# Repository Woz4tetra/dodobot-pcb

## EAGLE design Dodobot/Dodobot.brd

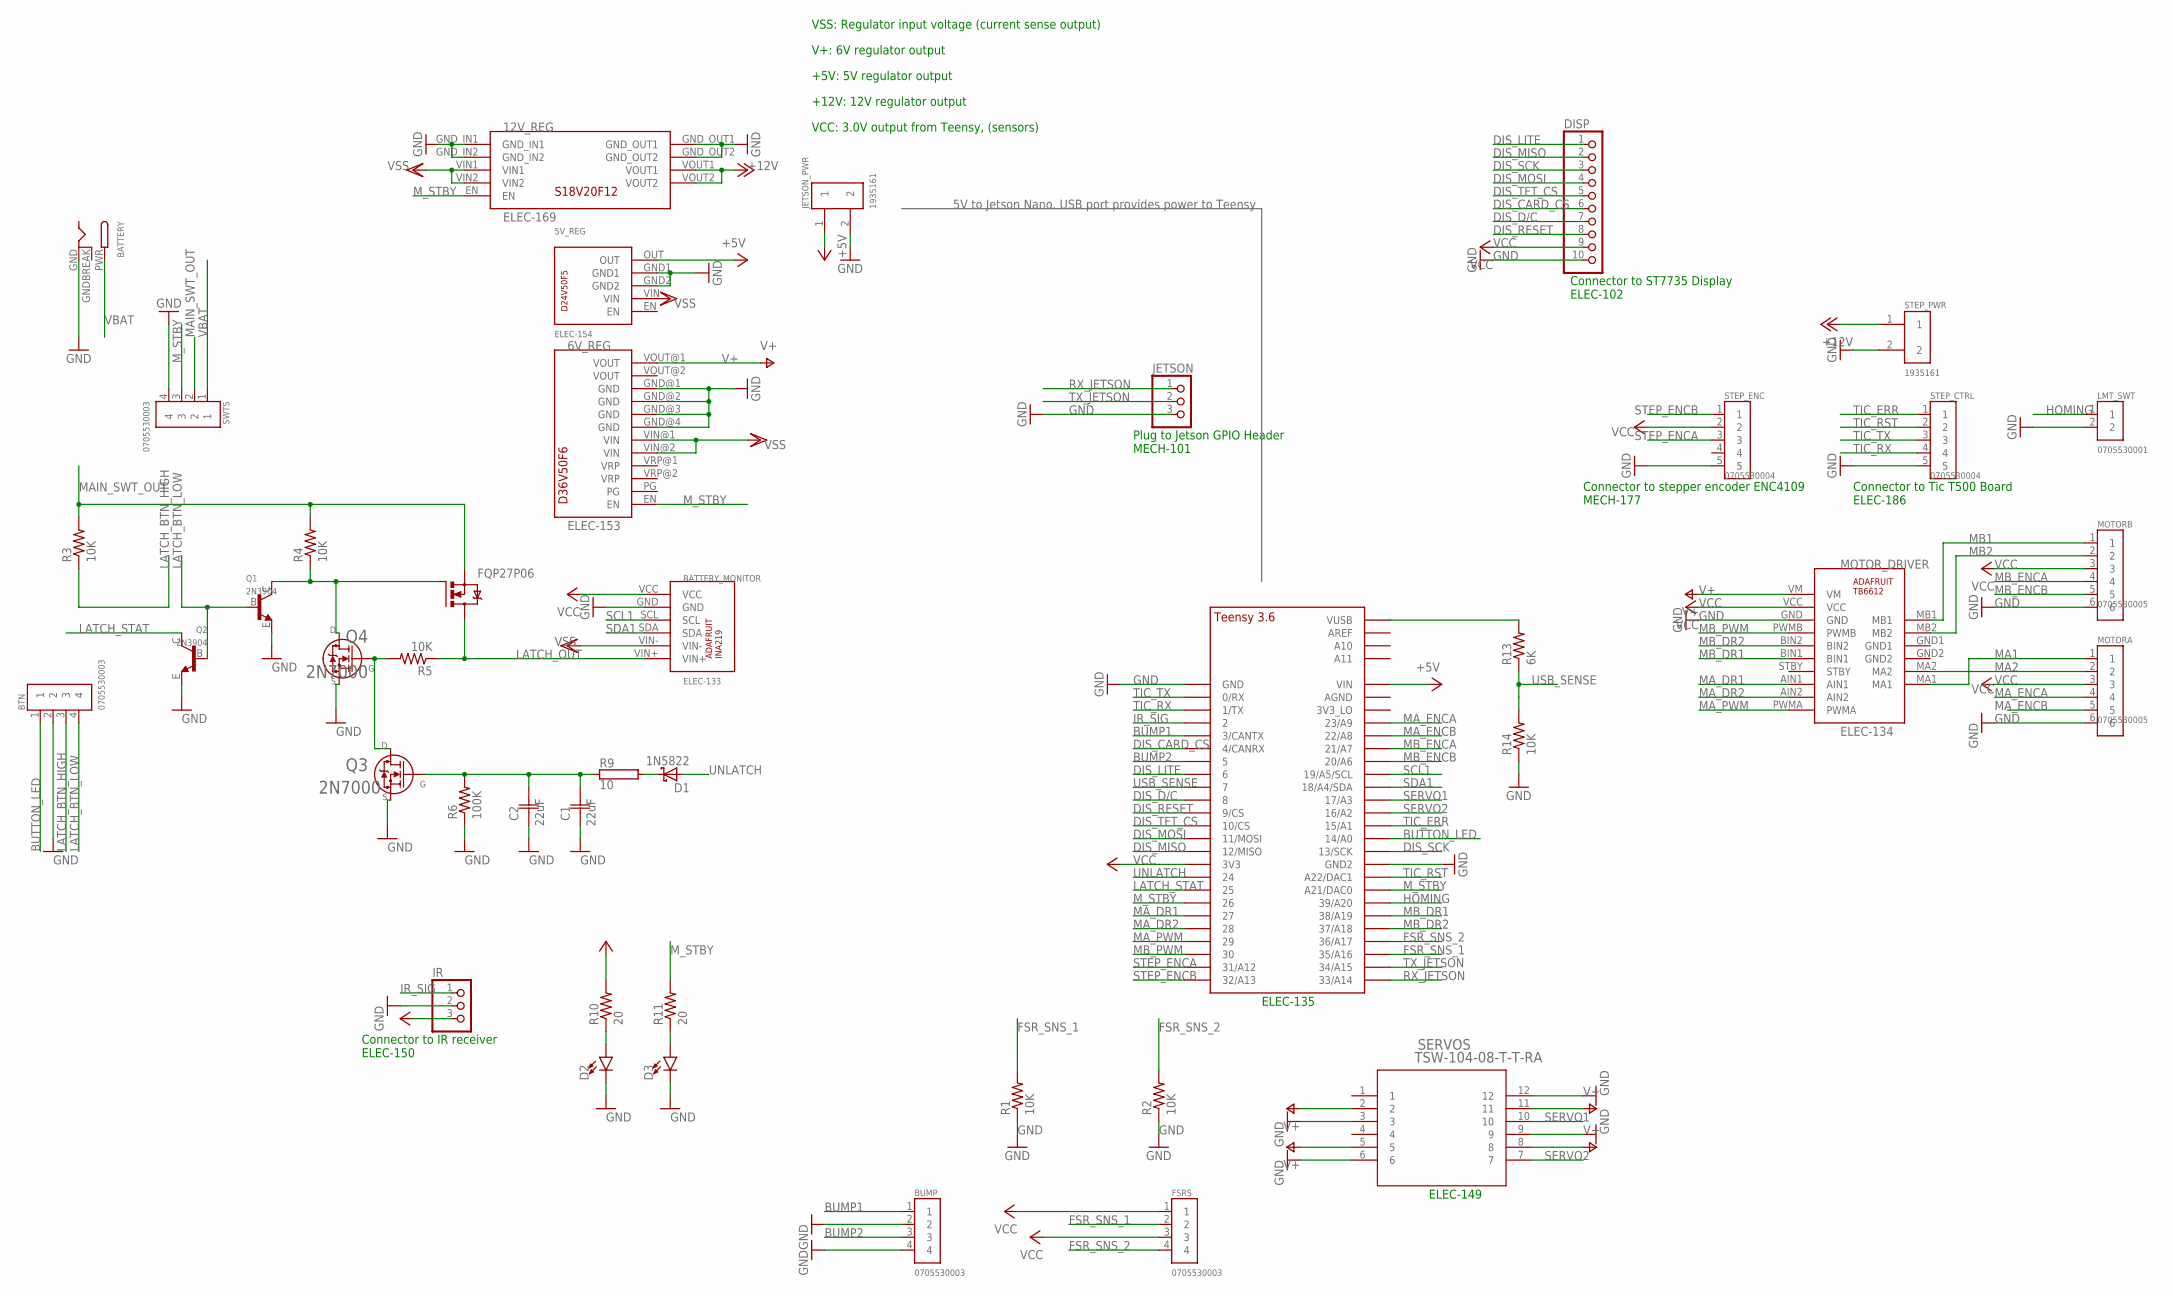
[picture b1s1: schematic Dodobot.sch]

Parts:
5V_REG: ELEC-154; D24V50F5
6V_REG: ELEC-153; D36V50FX
12V_REG: ELEC-169; S18V20FX
BATTERY: DCBARRELPTH; DCJACK_2MM_PTH
BATTERY_MONITOR: ELEC-133; INA219
BTN: 0705530003; MOLEX_0705530003
BUMP: 0705530003; MOLEX_0705530003
C1, C2: 22uF; CAP_R4525B
D1: 1N5822; DIOAD2120W130L950D530P
D2, D3: LED1206; LED-1206
DISP: PINHD-1X10; 1X10
FQP27P06: IRF530; TO220BV
FSRS: 0705530003; MOLEX_0705530003
IR: PINHD-1X3; 1X03
JETSON: PINHD-1X3; 1X03
JETSON_PWR: 1935161; PHOENIX_1935161
LMT_SWT: 0705530001; MOLEX_0705530001
MOTORA: 0705530005; MOLEX_0705530005
MOTORB: 0705530005; MOLEX_0705530005
MOTOR_DRIVER: ELEC-134; ADAFRUIT_TB6612
Q1, Q2: 2N3904; TO92
Q3, Q4: 2N7000; TO-92
R1, R2, R3, R4, R5, R14: 10K; RES_0805
R6: 100K; RES_0805
R9: 10; HPS58
R10, R11: 20; RES_1206
R13: 6K; RES_0805
SERVOS: TSW-104-08-T-T-RA; TSW-104-08-T-T-RA_SAI
STEP_CTRL: 0705530004; MOLEX_0705530004
STEP_ENC: 0705530004; MOLEX_0705530004
STEP_PWR: 1935161; PHOENIX_1935161
SWTS: 0705530003; MOLEX_0705530003
U$1: TEENSY_3.5/3.6_BASIC

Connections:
+5V: 5V_REG.OUT, JETSON_PWR.1, U$1.VIN
+12V: 12V_REG.VOUT1, 12V_REG.VOUT2, STEP_PWR.1
BUMP1: BUMP.1, U$1.3/CANTX
BUMP2: BUMP.3, U$1.5
BUTTON_LED: BTN.1, U$1.14/A0
DIS_CARD_CS: DISP.6, U$1.4/CANRX
DIS_D/C: DISP.7, U$1.8
DIS_LITE: DISP.1, U$1.6
DIS_MISO: DISP.2, U$1.12/MISO
DIS_MOSI: DISP.4, U$1.11/MOSI
DIS_RESET: DISP.8, U$1.9/CS
DIS_SCK: DISP.3, U$1.13/SCK
DIS_TFT_CS: DISP.5, U$1.10/CS
FSR_SNS_1: FSRS.2, R1.2, U$1.35/A16
FSR_SNS_2: FSRS.4, R2.2, U$1.36/A17
GND: 5V_REG.GND1, 5V_REG.GND2, 6V_REG.GND@1 (GND), 6V_REG.GND@2 (GND), 6V_REG.GND@3 (GND), 6V_REG.GND@4 (GND), 12V_REG.GND_IN1, 12V_REG.GND_IN2, 12V_REG.GND_OUT1, 12V_REG.GND_OUT2, BATTERY.GND, BATTERY_MONITOR.GND, BTN.2, BUMP.2, BUMP.4, C1.1, C2.1, D2.C, D3.C, DISP.10, IR.2, JETSON.3, JETSON_PWR.2, LMT_SWT.2, MOTORA.6, MOTORB.6, MOTOR_DRIVER.GND, Q1.E, Q2.E, Q3.1 (3), Q4.1 (3), R1.1, R2.1, R6.1, R14.1, SERVOS.3, SERVOS.6, SERVOS.9, SERVOS.12, STEP_CTRL.5, STEP_ENC.5, STEP_PWR.2, SWTS.4, U$1.GND, U$1.GND2
GNDBREAK: BATTERY.GNDBREAK
HOMING: LMT_SWT.1, U$1.39/A20
IR_SIG: IR.1, U$1.2
LATCH_BTN_HIGH: BTN.3, R3.1
LATCH_BTN_LOW: BTN.4, Q1.B, Q2.B
LATCH_OUT: BATTERY_MONITOR.VIN+, FQP27P06.D, R5.1
LATCH_STAT: Q2.C, U$1.25
MA1: MOTORA.1, MOTOR_DRIVER.MA1
MA2: MOTORA.2, MOTOR_DRIVER.MA2
MAIN_SWT_OUT: FQP27P06.S, R3.2, R4.2, SWTS.2
MA_DR1: MOTOR_DRIVER.AIN1, U$1.27
MA_DR2: MOTOR_DRIVER.AIN2, U$1.28
MA_ENCA: MOTORA.4, U$1.23/A9
MA_ENCB: MOTORA.5, U$1.22/A8
MA_PWM: MOTOR_DRIVER.PWMA, U$1.29
MB1: MOTORB.1, MOTOR_DRIVER.MB1
MB2: MOTORB.2, MOTOR_DRIVER.MB2
MB_DR1: MOTOR_DRIVER.BIN1, U$1.38/A19
MB_DR2: MOTOR_DRIVER.BIN2, U$1.37/A18
MB_ENCA: MOTORB.4, U$1.21/A7
MB_ENCB: MOTORB.5, U$1.20/A6
MB_PWM: MOTOR_DRIVER.PWMB, U$1.30
M_STBY: 6V_REG.EN, 12V_REG.EN, R11.2, SWTS.3, U$1.21/DAC0 (A21/DAC0), U$1.26
unnamed: D2.A, R10.1
unnamed: D3.A, R11.1
unnamed: FQP27P06.G, Q1.C, Q4.3 (2), R4.1
unnamed: Q3.3 (2), Q4.2 (1), R5.2
unnamed: D1.C, R9.2
unnamed: C1.2, C2.2, Q3.2 (1), R6.2, R9.1
unnamed: R13.2, U$1.VUSB
RX_JETSON: JETSON.1, U$1.33/A14
SCL1: BATTERY_MONITOR.SCL, U$1.19/A5/SCL
SDA1: BATTERY_MONITOR.SDA, U$1.18/A4/SDA
SERVO1: SERVOS.10, U$1.17/A3
SERVO2: SERVOS.7, U$1.16/A2
STEP_ENCA: STEP_ENC.3, U$1.31/A12
STEP_ENCB: STEP_ENC.1, U$1.32/A13
TIC_ERR: STEP_CTRL.1, U$1.15/A1
TIC_RST: STEP_CTRL.2, U$1.A22/DAC1
TIC_RX: STEP_CTRL.4, U$1.1/TX
TIC_TX: STEP_CTRL.3, U$1.0/RX
TX_JETSON: JETSON.2, U$1.34/A15
UNLATCH: D1.A, U$1.24
USB_SENSE: R13.1, R14.2, U$1.7
V+: 6V_REG.VOUT@1 (VOUT), MOTOR_DRIVER.VM, SERVOS.2, SERVOS.5, SERVOS.8, SERVOS.11
VBAT: BATTERY.PWR, SWTS.1
VCC: BATTERY_MONITOR.VCC, DISP.9, FSRS.1, FSRS.3, IR.3, MOTORA.3, MOTORB.3, MOTOR_DRIVER.VCC, R10.2, STEP_ENC.2, U$1.3V3
VSS: 5V_REG.VIN, 6V_REG.VIN@1 (VIN), 6V_REG.VIN@2 (VIN), 12V_REG.VIN1, 12V_REG.VIN2, BATTERY_MONITOR.VIN-

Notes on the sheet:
VSS: Regulator input voltage (current sense output)
V+: 6V regulator output
+12V: 12V regulator output
+5V: 5V regulator output
5V to Jetson Nano. USB port provides power to Teensy
VCC: 3.0V output from Teensy, (sensors)
Plug to Jetson GPIO Header MECH-101
ELEC-135
Connector to ST7735 Display ELEC-102
Connector to Tic T500 Board ELEC-186
Connector to stepper encoder ENC4109 MECH-177
ELEC-149
Connector to IR receiver ELEC-150

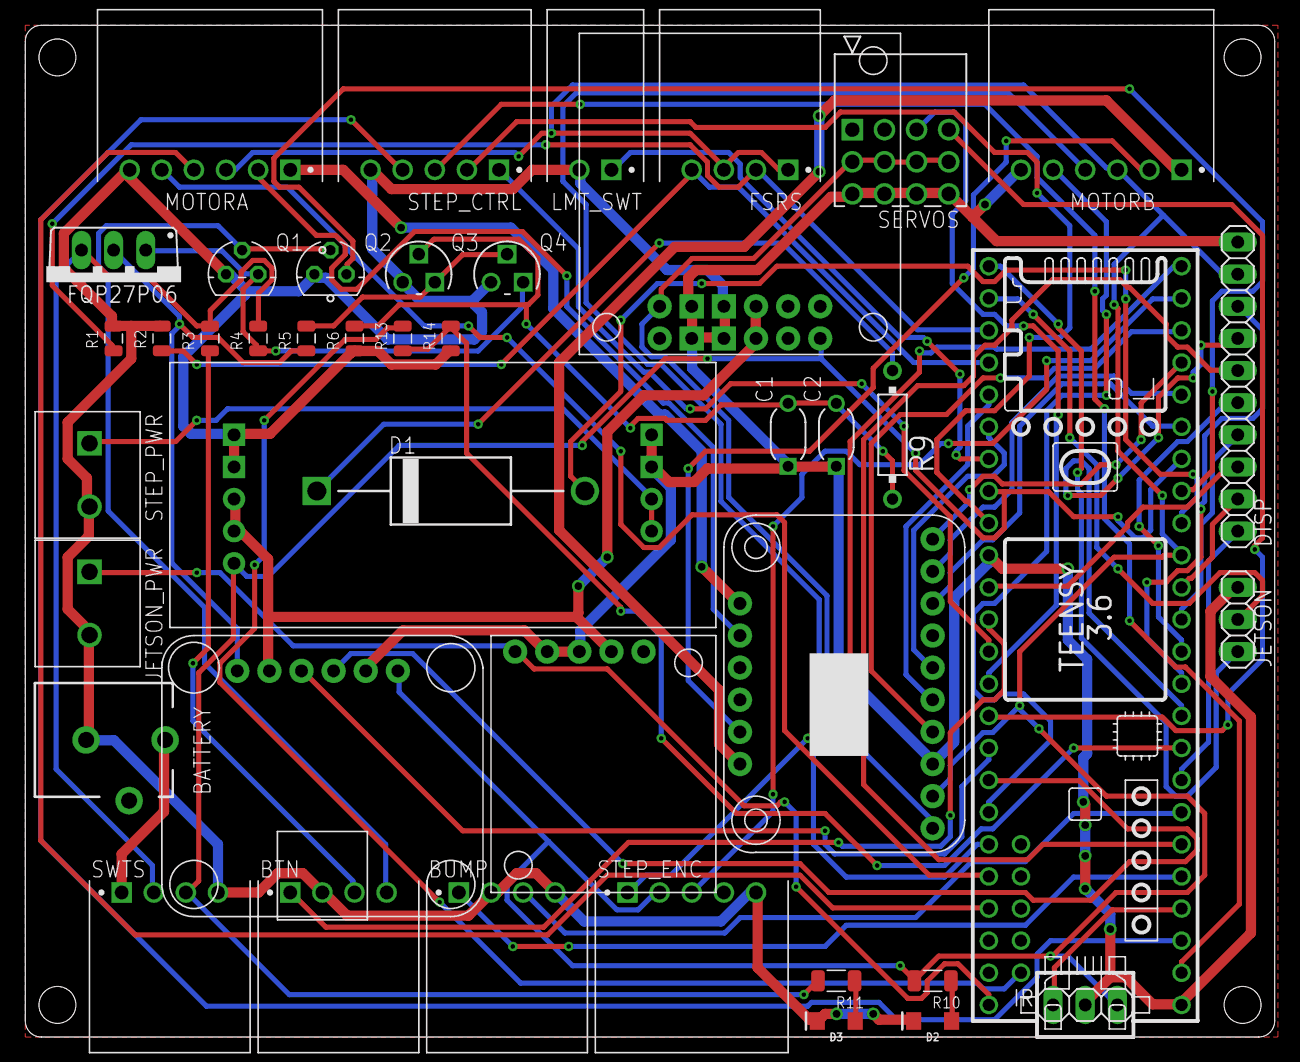
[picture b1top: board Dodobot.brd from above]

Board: 2 copper layers, 98.8 x 80.0 mm, 43 parts (0 on the bottom side), 63 nets.

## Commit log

2020-07-23 Rev 1
2020-07-23 Restoring Rev 2 changes
    Adding stepper encoder
    Increased tracewidth size
    Added VIN trace to teensy
    changed from 40-pin bus to 3 pin header
2020-08-01 fixing top connector positioning
2020-08-03 minor fixes. Correcting errors in library files

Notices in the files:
parts and their libraries:
SparkFun-LED: Licensing: Creative Commons ShareAlike 4.0 International - https://creativecommons.org/licenses/by-sa/4.0
